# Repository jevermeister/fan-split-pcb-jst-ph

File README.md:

This is a fan splitter PCB for the Hex-Zero Manta Ray Bed. You of course can use it also for whichever purposes but that's what I made it for.

You will need 3x JST S2B-PH-K-S for this.
Send the gerber zip file to JLCPCB and you're good to go.

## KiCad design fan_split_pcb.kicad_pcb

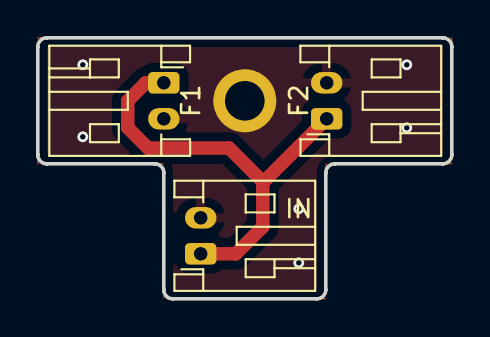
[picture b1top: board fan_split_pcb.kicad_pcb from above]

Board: 2 copper layers, 23.0 x 14.5 mm, 3 parts (0 on the bottom side), 2 nets.

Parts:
F1: PWR_OUT1; JST_PH_S2B-PH-K_1x02_P2.00mm_Horizontal
F2: PWR_OUT2; JST_PH_S2B-PH-K_1x02_P2.00mm_Horizontal
IN: PWR_IN; JST_PH_S2B-PH-K_1x02_P2.00mm_Horizontal

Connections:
GND: F1.2, F2.2, IN.2
VDD: F1.1, F2.1, IN.1

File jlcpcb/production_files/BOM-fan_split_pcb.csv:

Comment,Designator,Footprint,LCSC,Quantity
PWR_OUT1,F1,JST_PH_S2B-PH-K_1x02_P2.00mm_Horizontal,,1
PWR_OUT2,F2,JST_PH_S2B-PH-K_1x02_P2.00mm_Horizontal,,1

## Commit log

2025-02-28 added kicad files
2025-02-28 modified m2 mounting hole and added production files
